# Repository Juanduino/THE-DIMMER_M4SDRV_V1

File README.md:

# THE DIMMER_M4SDRV_V1
Linear BLDC motor controller with TMC2209 for rotation dev. based on SAMD(E)51 MCU. The primary goal of this project is to make a linear motor controller, which can control the (single or multiple) Z axis and rotation on openPnP machines. With that said, the hardware could be used to control other (sub 10amp) 3 phase motors or steppers. In the openPnP community, there has been development on multi-nozzle machines for some time. This is an attempt to simplify and specify the hardware for openPnP machines.

By introducing sub-controllers in openPnP, it is now possible to delegate various tasks to various controllers. This project builds on that feature. Each z-axis subcontroller, will connect to the mainframe by either USB or CAN

Files are made with Kicad Nightly Build. If you have the latest stable releace installed, you can install the Nightly build next to it in eg. KicadNightly folder. Just dont install systam variables, which is chosen in the install guide.

PROS: 

By using a linear 3 phase motor controller with an onboard stepper IC for rotation, wires can be kept very short.
 
The linear motor is easy to make yourself with common 3mm long neodymium magnets. (Onboard Hall sensors is spaced apart, with the appropriate distance for these magnets). Likewise a external (angle)sensor can be connected via SPI, I2C or Serial.
 
To make the motor, the idea is to fill up a eg. stainless steel pipe with magnets and spacers between those magnets. The coils of the motor will be wound on a 3D printed "slider" (bushing) with the appropriate spacing to match the magnet's length (3mm).
 
By winding the coils around the magnets, the entire pull/push of the magnets is used and the linear motor is not as sensitive to the distance between coils and magnets.
 
The south and north pole of the coils will be in the direction of movement, unlike normal BLDC motors, where you make two windings for each pole pair.
 
Mosfets have quite different specs. when it comes to voltages and current ratings. If using 12v or 24v for a motor, its better to use 30v rated mosfets with a much lower Rds(on) (resistence) compared to higher voltage rated MOSFETS. 
The amount of heat dissipated from the Mosfets can be calculated. (see page 3 https://d1d2qsbl8m0m72.cloudfront.net/en/products/databook/applinote/ic/power/switching_regulator/power_loss_appli-e.pdf)

CONS: It takes time to perfect. All good cookies take time to make. The intended Arduino Library (SimpleFoc) needs further development to be able to work with inline current sensing.

Changelog:

Added BusBar footprint for 1.5mm copper wire. This add´s some 50amp rating to the VIN line. (@10C rise)

Mosfets are rated for MAX 60amp pulsed current.

Added MAX40056 Current sensor on 3 out of 4 phases. The last fase will have to follow one of the ones with sensor if used seperately. In stepper configuration, the sensor will monitor the two windings on two bidirectional sensors.
In 3 phase configuration, the 3 current sensors will be in use. The MAX40056 has advanced PWM rejection, and ultra fast settle time. This ensures a good read in harsh PWM invironments.

Added MOSFET driver MIC4605-2 which control high side & Low side using one PWM input. This mean we can use the SimpelFOC lib. as is (Current sense still need implementation).
This driver is not just fast its totally fast. Combined with the ultra low Gate charge and rise/fall time of the Infinion Mosfets, hopefully this will keep things cool.
 
Note: Adafruit is adding support for SAME51, which has native CAN FD support.
(source: https://github.com/adafruit/ArduinoCore-samd/pull/267)

HARDWARE:

SAME51 MCU 120 mhz M4 architecture with CAN FD (https://www.microchip.com/wwwproducts/en/ATSAME51J20A)

TMC2209 stepper driver (https://www.trinamic.com/products/integrated-circuits/details/tmc2209-la/)

MOSFETS BSC0925ND Dual channal 40amp 17nC gate charge (https://www.infineon.com/cms/en/product/power/mosfet/12v-300v-n-channel-power-mosfet/bsc0925nd/)

Gate drivers MIC4605-2 PWM indput (https://www.microchip.com/wwwproducts/en/MIC4605)

Current sensors MAX40056 (https://datasheets.maximintegrated.com/en/ds/MAX40056F-MAX40056U.pdf)

Step-Down converter 4v/36v to 10v rail 1amp (https://www.ti.com/product/LMR50410)

3.6v LDO 500mA (https://ww1.microchip.com/downloads/en/DeviceDoc/MIC5219-500mA-Peak-Output-LDO-Regulator-DS20006021A.pdf)

3 x ANALOG HALL sensors (https://www.ti.com/product/DRV5053?qgpn=drv5053)

Analog hall sensors will potentially give a precision of the ADC resolution over one polepair. Thats 12bit (4096:1) (3mm/4096=0,0007mm)

CAN FD physical layer IC MCP2562FD-E_SN 8Mbps (https://www.microchip.com/wwwproducts/en/MCP2562FD)

4 layer PCB w. 105µm outer copper. (Min 0.25 mm. trace width and clearence)

Communication ports:

SERCOM port can be configuered to I2C, SPI and serial.

CAN FD is integrated into the SAME51 MCU.

USB 2.0 full speed. (USB port data-pins is broken out)

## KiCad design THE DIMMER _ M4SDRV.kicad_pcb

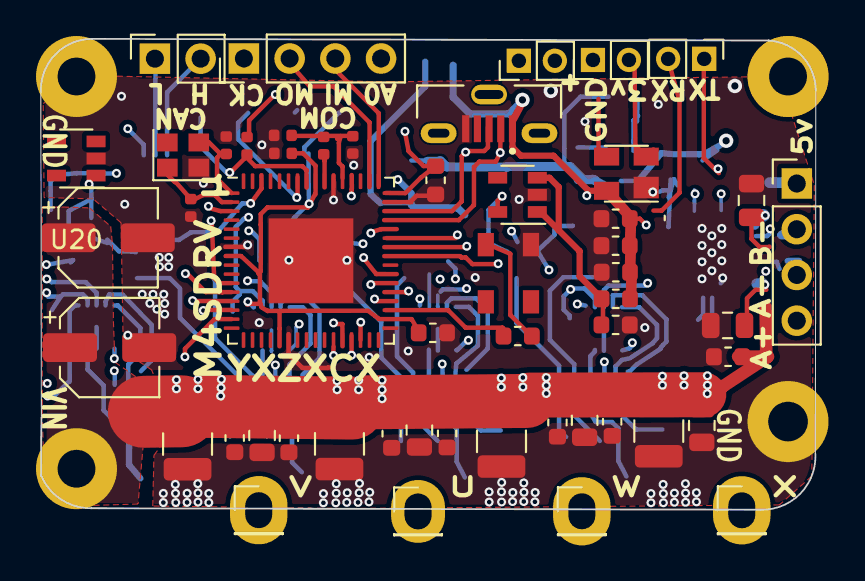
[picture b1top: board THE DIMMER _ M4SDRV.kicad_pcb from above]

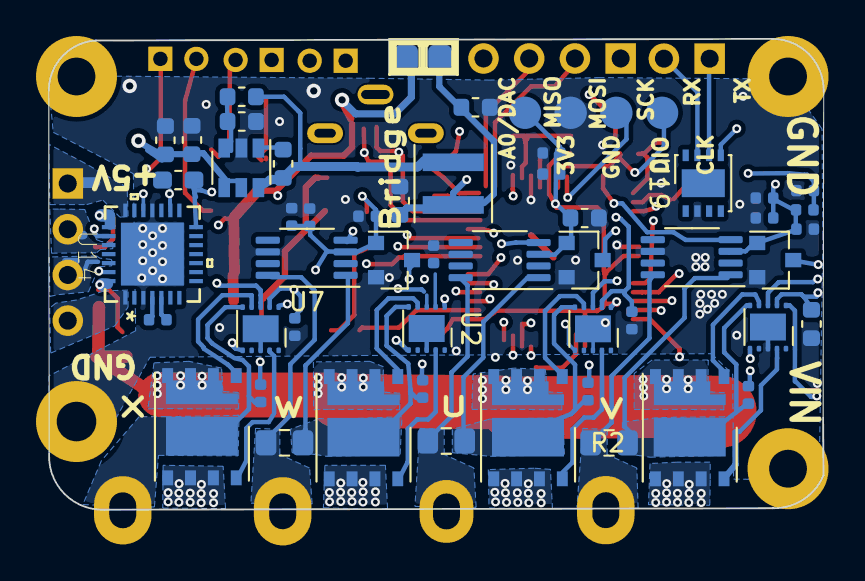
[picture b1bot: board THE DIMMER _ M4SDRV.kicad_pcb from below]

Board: 4 copper layers, 43.1 x 26.2 mm, 106 parts (51 on the bottom side), 68 nets.

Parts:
C1, C2, C12, C13, C16, C19, C30, C31, C33, C34, C35, C36, C37, C39, C41, C43, C44, C45: 1uF; C_0402_1005Metric
C3: 1nF; C_0603_1608Metric
C4, C6, C14, C17, C28, C28#2, C32: 1uF; C_0603_1608Metric
C5, C29: 100nF; C_0603_1608Metric
C7, C8, C10, C18: 10uF; C_1210_3225Metric
C11: 10uF; C_0402_1005Metric
C15: 10uF; C_0603_1608Metric
C20: 47; CP_Elec_5x5.8
C21: 47uF; CP_Elec_5x5.8
C22, C22#2: 1uF7; C_0603_1608Metric
C23, C24: 10nF; C_0603_1608Metric
C25, C25#2, C26, C27: 4.7uF; C_0805_2012Metric
C38, C40, C42: 10nF; C_0402_1005Metric
C46: 2.2uF; C_0603_1608Metric
C47, C50, C51: 200nF; C_0603_1608Metric
C49: 0.1uF; C_0603_1608Metric
D1: PRTR5V0U2X; SOT-143
FB2: 120r/0.85A; C_0603_1608Metric
H1, H2, H3, H4: MountingHole_Pad; MountingHole_2.2mm_M2_ISO14580_Pad_TopBottom
J1, J5, J6, J11: Conn_01x01; PinHeader_1x01_P2.54mm_Vertical
J2: USB_B_Micro; MOLEX_1051330001
J3: Conn_01x05; PinHeader_1x04_P2.54mm_Vertical
J4: Conn_01x02; PinSocket_1x02_P2.54mm_Vertical
J7: Conn_01x04; PinHeader_1x04_P2.54mm_Vertical
J8, J8#2, J12: Conn_01x02; PinHeader_1x02_P2.00mm_Vertical
J9: Conn_01x04; POGO
J10: GS2; R_0805_2012Metric
L1: L; L_0402_1005Metric
L2: 33uH; L_Coilcraft_XxL4020
LED1: IN-PI33TBTPRPGPB_; IN-PI33TBTPRPGPB
R1: 100k; R_0603_1608Metric
R2, R3, R8: 0.02ohm; R_0805_2012Metric_Pad1.15x1.40mm_HandSolder
R4: 2k; R_0603_1608Metric
R5, R6: 10k; R_0402_1005Metric
R7: 11.11k; R_0603_1608Metric
R19, R20: 0R11; R_0805_2012Metric
R21: 1k 1%; R_0603_1608Metric_Pad1.05x0.95mm_HandSolder
U1: ATSAMD51J19A-M; QFN-64-1EP_9x9mm_P0.5mm_EP4.7x4.7mm
U2, U15, U16, U17: MIC4605-2YMT; MIC4605
U3: LMR50410; SOT-23-6
U4, U5, U6, U18: BSC0925NDATMA1; Infineon_PG-TISON-8-2
U7, U12, U13: MAX40056_uMAX8; MAX40056F
U8: MIC5219-3.6; SOT-23-5
U9, U10, U11: DRV5053; SOT-23
U14: TMC2209-LA
U19: MCP2562FD-E_SN; DFN-8-1EP_3x3mm_P0.65mm_EP1.55x2.4mm
U20: LF15_TO220; SOT-23-5
Y1: Crystal_GND2_Small; Crystal_SMD_2520-4Pin_2.5x2.0mm

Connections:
+3V3: C12.1, C13.1, C14.1, C15.1, C16.1, C17.1, C38.2, C39.2, C40.2, C41.2, C42.2, C43.2, J9.4, R5.2, R6.2, U1.8 (VDDANA), U1.21 (VDDIOB), U1.34 (VDDIO), U1.48 (VDDIO), U1.56 (VDDIO), U2.1 (EN), U7.3 (VDD), U8.5 (OUT), U9.1 (VCC), U10.1 (VCC), U11.1 (VCC), U12.3 (VDD), U13.3 (VDD), U15.1 (EN), U16.1 (EN), U17.1 (EN), U19.5 (VIO)
+5V: U19.3 (VDD), U20.3 (VO)
/+5v_filtered: C5.1, FB2.2, U8.1 (IN), U8.3 (EN)
A0/DAC0/CS: J3.4, U1.3 (PA02)
A1: U1.14 (PA05), U9.3 (Vout)
A2: U1.11 (PB08), U7.4 (OUT)
A3: U1.12 (PB09), U13.4 (OUT)
A4: U1.13 (PA04), U11.3 (Vout)
A5: U1.15 (PA06), U10.3 (Vout)
A6: U1.62 (PB01), U12.4 (OUT)
CAN1_RX: U1.28 (PB15), U19.4 (RXD)
CAN1_STANDBY: U1.26 (PB13), U19.8 (STBY)
CAN1_TX: U1.27 (PB14), U19.1 (TXD)
CAN_H: J4.2, U19.7 (CANH)
CAN_L: J4.1, U19.6 (CANL)
D+: D1.3 (IO2), J2.3 (D+), J8.2, J8#2.2, U1.46 (PA25)
D-: D1.2 (IO1), J2.2 (D-), J8.1, J8#2.1, U1.45 (PA24)
DA1: J7.2, U14.24 (OA1)
DA2: J7.1, U14.21 (OA2)
DB1: J7.3, U14.26 (OB1)
DB2: J7.4, U14.1 (OB2)
DIR: U1.37 (PA18), U14.19 (DIR)
GND: C1.1, C2.2, C3.2, C4.2, C5.2, C6.2, C7.1, C8.1, C10.1, C11.2, C12.2, C13.2, C14.2, C15.2, C16.2, C17.2, C18.1, C20.2, C21.2, C22.1, C22#2.1, C23.1, C24.1, C25.1, C25#2.1, C26.1, C27.1, C28.1, C28#2.1, C29.1, C30.1, C31.1, C32.2, C33.2, C34.2, C38.1, C39.1, C40.1, C41.1, C42.1, C43.1, C44.2, C46.2, C47.2, C50.2, C51.2, D1.1 (GND), H3.1, H4.1, J2.5 (GND), J9.3, LED1.1 (GND), R7.2, R19.1, R20.1, U1.7 (GNDANA), U1.22 (GND), U1.33 (GND), U1.47 (GND), U1.54 (GND), U1.65 (GND), U2.8 (VSS), U3.2 (PGND), U4.5 (S2(gnd)), U4.6 (S2(gnd)), U4.7 (S2(gnd)), U5.5 (S2(gnd)), U5.6 (S2(gnd)), U5.7 (S2(gnd)), U6.5 (S2(gnd)), U6.6 (S2(gnd)), U6.7 (S2(gnd)), U7.6 (GND), U8.2 (GND), U9.2 (GND), U10.2 (GND), U11.2 (GND), U12.6 (GND), U13.6 (GND), U14.3 (GND), U14.18 (GND), U14.29 (EPAD), U15.8 (VSS), U16.8 (VSS), U17.8 (VSS), U18.5 (S2(gnd)), U18.6 (S2(gnd)), U18.7 (S2(gnd)), U19.2 (VSS), U20.2 (GND), Y1.2
HB1_HO: U2.4 (HO), U4.1 (G1(GHS))
HB1_LO: U2.9 (LO), U4.8 (G2(GLD))
HB2_HO: U5.1 (G1(GHS)), U15.4 (HO)
HB2_LO: U5.8 (G2(GLD)), U15.9 (LO)
HB3_HO: U6.1 (G1(GHS)), U16.4 (HO)
HB3_LO: U6.8 (G2(GLD)), U16.9 (LO)
HB4_HO: U17.4 (HO), U18.1 (G1(GHS))
HB4_LO: U17.9 (LO), U18.8 (G2(GLD))
LED RGB IN-PI33TBTPRPGPB: R4.1, U1.35 (PA16)
unnamed: C2.1, C11.1, L1.1, U1.53 (VDDCORE)
unnamed: C19.1, U14.4 (CPO)
unnamed: C19.2, U14.5 (CPI)
unnamed: C30.2, U1.1 (PA00), Y1.3
unnamed: C31.2, U1.2 (PA01), Y1.1
unnamed: C35.1, U2.3 (HB)
unnamed: C36.1, U15.3 (HB)
unnamed: C37.1, U16.3 (HB)
unnamed: C45.1, U17.3 (HB)
unnamed: C49.1, L2.1, R1.1, U3.6 (SW)
unnamed: C49.2, U3.1 (CB)
unnamed: L1.2, U1.55 (VSW)
unnamed: LED1.2 (DIN), R4.2
unnamed: R1.2, R7.1, U3.3 (FB)
unnamed: R19.2, U14.27 (BRB)
unnamed: R20.2, U14.23 (BRA)
RESET: C1.2, R5.1, U1.52 (~RESET)
SPI_MISO: J3.3, U1.49 (PB22)
SPI_MOSI: J3.2, U1.50 (PB23)
SPI_SCK: J3.1, U1.36 (PA17)
STEP: U1.38 (PA19), U14.16 (STEP)
SWCLK: J9.1, R6.1, U1.57 (PA30)
SWDIO: J9.2, U1.58 (PA31)
TCC0_CH0/Switch 1: U1.41 (PA20), U2.6 (PWM)
TCC0_CH1/Switch 2: U1.42 (PA21), U17.6 (PWM)
TCC0_CH3/Switch 4: U1.44 (PA23), U15.6 (PWM)
TCC0_CH5/Switch 6: U1.39 (PB16), U16.6 (PWM)
U: C37.2, J6.1, R3.1, R3.2, U6.9 (Vphase), U13.1 (¨RS+), U13.8 (RS), U16.5 (HS)
UART_RX: J12.2, R21.1, U1.30 (PA13), U14.14 (PDN_UART)
UART_TX: J12.1, R21.2, U1.29 (PA12)
V: C36.2, J5.1, R2.1, R2.2, U5.9 (Vphase), U12.1 (¨RS+), U12.8 (RS), U15.5 (HS)
VBUS: C3.1, C4.1, C6.1, D1.4 (VCC), FB2.1, H1.1, J2.1 (VBUS), J10.2 (G2)
VIN: C7.2, C8.2, C10.2, C18.2, C20.1, C21.1, C22.2, C22#2.2, C23.2, C24.2, C25.2, C25#2.2, C26.2, C27.2, C28.2, C28#2.2, C29.2, C46.1, C47.1, H2.1, U3.4 (EN), U3.5 (VIN), U4.2 (D1(Vin)), U5.2 (D1(Vin)), U6.2 (D1(Vin)), U14.22 (VS), U14.28 (VS), U18.2 (D1(Vin))
VOUT/10v: C32.1, C33.1, C34.1, C44.1, C50.1, C51.1, J10.1 (G1), L2.2, U2.2 (VDD), U15.2 (VDD), U16.2 (VDD), U17.2 (VDD), U20.1 (VI)
W: C35.2, J1.1, R8.1, R8.2, U2.5 (HS), U4.9 (Vphase), U7.1 (¨RS+), U7.8 (RS)
X: C45.2, J11.1, U17.5 (HS), U18.9 (Vphase)

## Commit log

2020-09-30 Added files
2020-09-30 Add 3D model
2020-09-30 Change Tipo
2020-10-06 Added curretn sensor and driver
    Added current sensor MAX40056 and MOSFET driver MIC4605-2YMT.
2020-10-07 Added 4th Bridge
    This adds support for controlling steppers using SimpelFOC lib. Yes with 40 amp rated bridges. Added current sensors, which will be sensitive in the low regions.
2020-10-07 Create ADD_driver and current sensor.PNG
    TOP side
2020-10-08 Better to have USB facing out, if the boards are mounted on a pnp head
2020-10-09 added switching regulator for 10v gate rail
2020-11-03 Dev.
2020-11-17 Update Dimensions.PNG
    Almost there. Added a few millimeters to make room for the CAN FD tranciever and USB data lines. The dimensions is still way within the NEMA17 width, which should give access to the NEMA17 assembly b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

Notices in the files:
parts and their libraries:
Copyright 2016 Accelerated Designs. All rights reserved.
